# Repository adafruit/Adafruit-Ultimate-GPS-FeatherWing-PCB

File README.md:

## Adafruit Ultimate GPS FeatherWing PCB
<a href="http://www.adafruit.com/products/3133"><br/>
Click here to purchase one from the Adafruit shop</a>

The Adafruit Ultimate GPS FeatherWing plugs right into your Feather board and gives it a precise, sensitive, and low power GPS module for location identifcation anywhere in the world. As a bonus, the GPS can also keep track of time once it is synced with the satellites.

Works with all Feathers except for those with USB-Serial converters that use the UART pins. Right now that means the ESP8266 Huzzah Feather and nRF52 Feather don't work

PCB files for the Adafruit Ultimate GPS FeatherWing. The format is EagleCAD schematic and board layout
- https://www.adafruit.com/products/3133

### License

Adafruit invests time and resources providing this open source design, please support Adafruit and open-source hardware by purchasing products from [Adafruit](https://www.adafruit.com)!

All text above must be included in any redistribution

Designed by Limor Fried/Ladyada for Adafruit Industries.
Creative Commons Attribution/Share-Alike, all text above must be included in any redistribution. 
See license.txt for additional information.

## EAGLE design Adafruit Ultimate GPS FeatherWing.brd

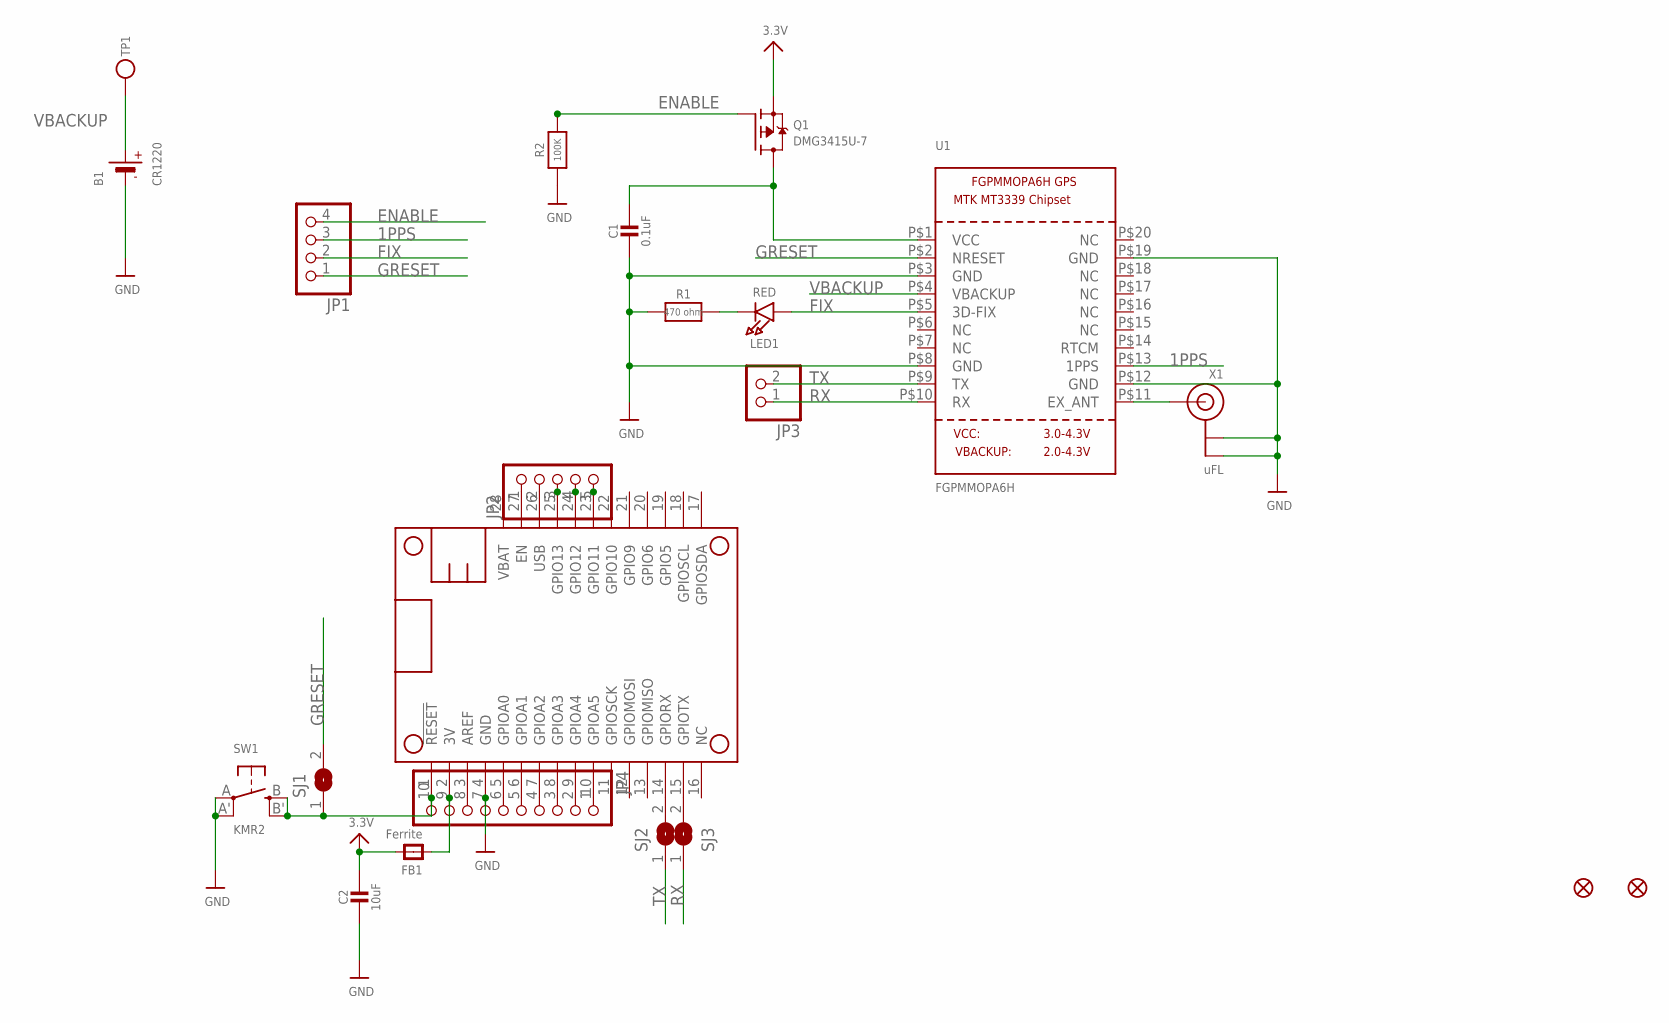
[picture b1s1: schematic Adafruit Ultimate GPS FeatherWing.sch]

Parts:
B1: CR1220; CR1220-2
C1: 0.1uF; 0805-NO
C2: 10uF; 0805-NO
FB1: Ferrite; 0805-NO
FID1, FID2: FIDUCIAL""; FIDUCIAL_1MM
JP1: HEADER-1X4ROUND; 1X04_ROUND
JP2: HEADER-1X570MIL; 1X05_ROUND_70
JP3: HEADER-1X2ROUND; 1X02_ROUND
JP4: HEADER-1X10ROUND; 1X10_ROUND
LED1: RED; CHIPLED_0805_NOOUTLINE
MS1: FEATHERWING
Q1: DMG3415U-7; SOT23-WIDE
R1: 470 ohm; 0805-NO
R2: 100K; 0805-NO
SJ1: SOLDERJUMPER; SOLDERJUMPER_ARROW_NOPASTE
SJ2, SJ3: SOLDERJUMPERCLOSED; SOLDERJUMPER_CLOSEDWIRE
SW1: KMR2; BTN_KMR2_4.6X2.8
TP1: TESTPOINTROUND1.5MM; TESTPOINT_ROUND_1.5MM
U1: FGPMMOPA6H
X1: uFL; U.FL

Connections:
1PPS: JP1.3, U1.P$13 (1PPS)
3.3V: C2.1, FB1.2, Q1.2 (S)
3V: FB1.1, JP4.9, MS1.2 (3V)
ENABLE: JP1.4, Q1.1 (G), R2.2
FIX: JP1.2, LED1.A, U1.P$5 (3D-FIX)
GND: B1.-, C1.2, C2.2, JP4.7, MS1.4 (GND), R1.1, R2.1, SW1.A, SW1.A' (P1), U1.P$3 (GND), U1.P$8 (GND), U1.P$12 (GND), U1.P$19 (GND), X1.1 (GND), X1.2 (GND)
GRESET: JP1.1, SJ1.2, U1.P$2 (NRESET)
unnamed: JP2.3, MS1.25 (GPIO13)
unnamed: LED1.C, R1.2
unnamed: JP2.4, MS1.24 (GPIO12)
unnamed: U1.P$11 (EX_ANT), X1.3 (SIGNAL)
unnamed: JP2.5, MS1.23 (GPIO11)
unnamed: JP4.1, MS1.10 (GPIOA5)
unnamed: JP4.2, MS1.9 (GPIOA4)
unnamed: JP4.3, MS1.8 (GPIOA3)
unnamed: JP4.4, MS1.7 (GPIOA2)
unnamed: JP4.5, MS1.6 (GPIOA1)
unnamed: JP4.6, MS1.5 (GPIOA0)
unnamed: JP4.10, MS1.1 (!RESET), SJ1.1, SW1.B (S), SW1.B' (S1)
unnamed: JP4.8, MS1.3 (AREF)
unnamed: JP2.1, MS1.27 (EN)
unnamed: C1.1, Q1.3 (D), U1.P$1 (VCC)
unnamed: MS1.14 (GPIORX), SJ2.2
unnamed: MS1.15 (GPIOTX), SJ3.2
RX: JP3.1, SJ3.1, U1.P$10 (RX)
TX: JP3.2, SJ2.1, U1.P$9 (TX)
USB: JP2.2, MS1.26 (USB)
VBACKUP: B1.+, TP1.P$1, U1.P$4 (VBACKUP)

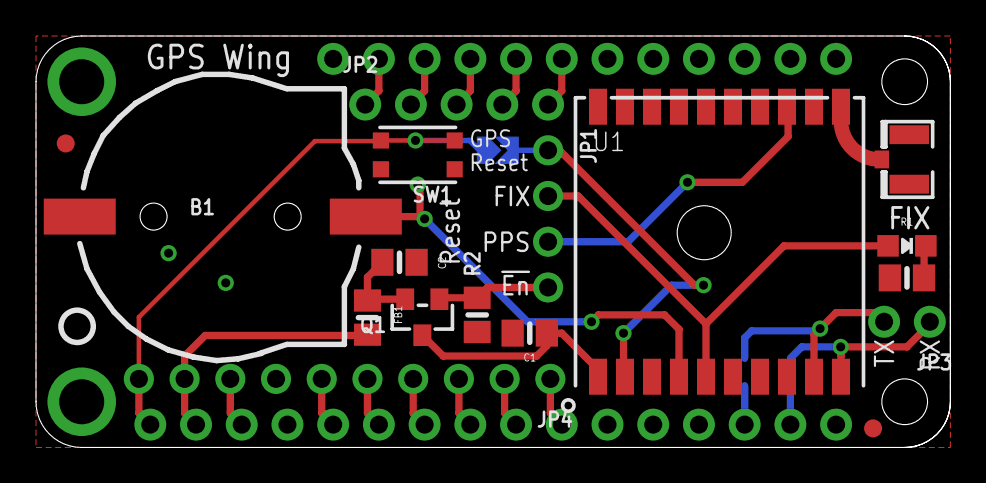
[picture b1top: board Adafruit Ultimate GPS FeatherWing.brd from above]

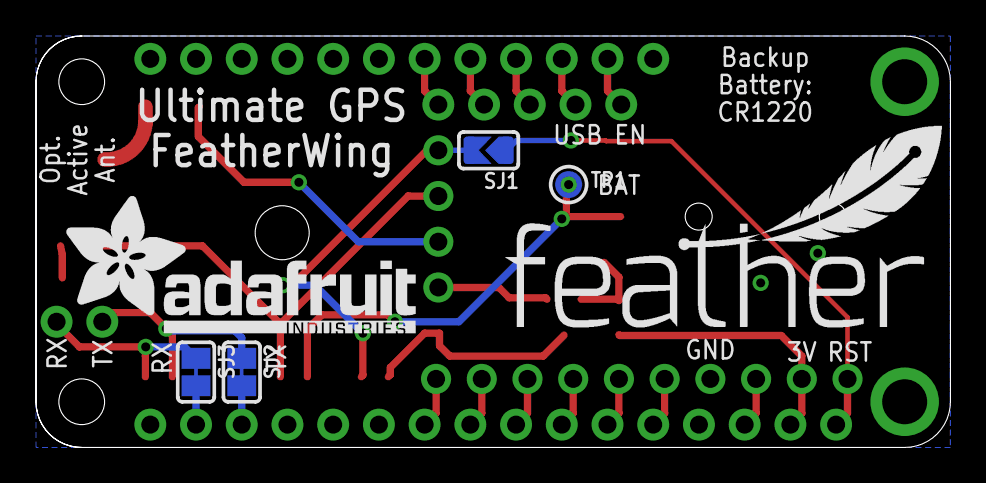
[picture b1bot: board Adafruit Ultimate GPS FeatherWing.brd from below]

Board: 2 copper layers, 50.8 x 22.9 mm, 25 parts (6 on the bottom side), 28 nets.

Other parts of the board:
U$9: PCBFEAT-REV-040
U$10: FEATHERLOGO
U$11: ADAFRUIT_TEXT_20MM

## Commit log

2016-05-17 init
2016-05-17 woot
